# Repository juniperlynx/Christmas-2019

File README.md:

# 2019 Christmas Cards

Software and board layouts for my 2019 Christmas cards. These use an AtTiny84 to drive a 4x5 Charlieplexed LED array to display messages and run on a CR2032 coin cell. A cutout is included to hang them up.

Board design, software, and logo graphics by Juniper Starr and licensed CC BY 4.0. Graphics made with the Snowtop Caps font are property of [Deiter Steffmann](http://www.steffmann.de) and are free for noncommercial use only.

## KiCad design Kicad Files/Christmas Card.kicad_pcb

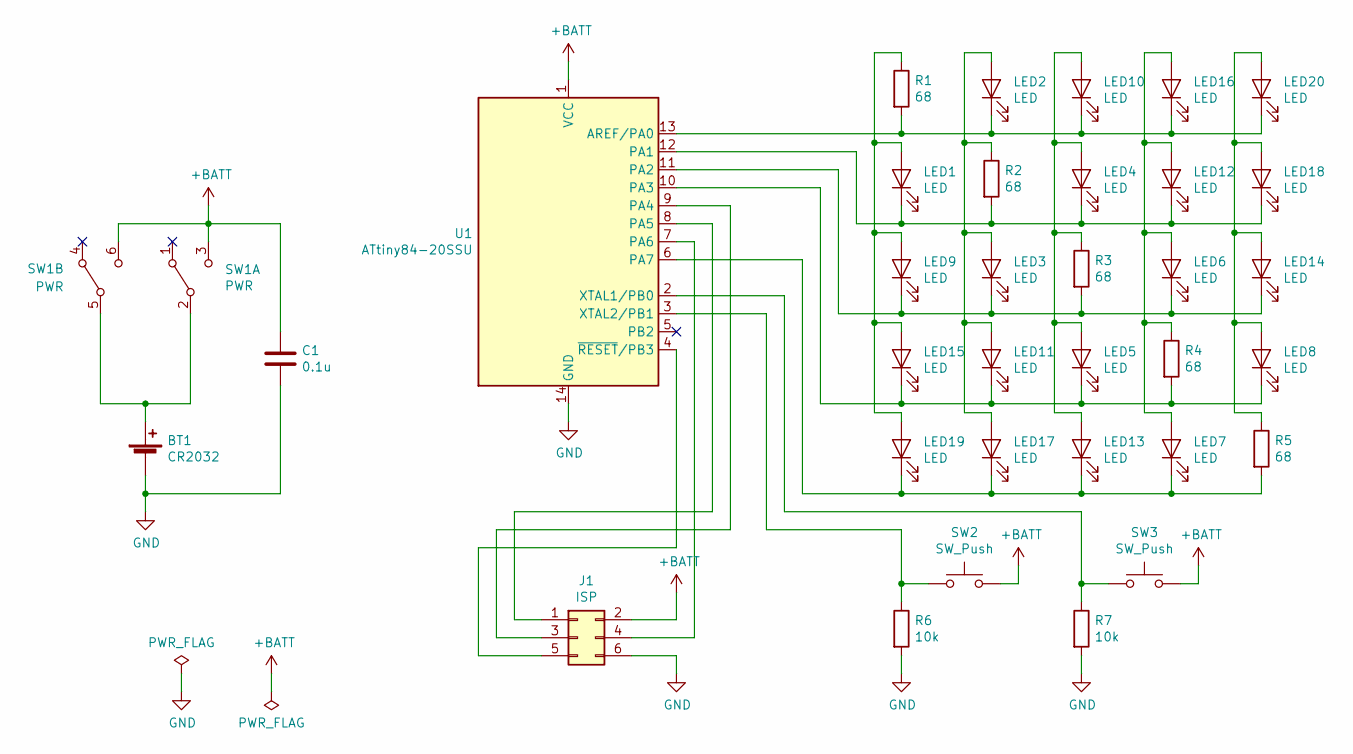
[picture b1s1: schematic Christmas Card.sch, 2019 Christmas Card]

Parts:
BT1: CR2032; BatteryStrap BC-2003-G-TR
C1: 0.1u; C_0805_2012Metric
J1: ISP; PinHeader_2x03_P2.54mm_Vertical
LED1, LED2, LED3, LED4, LED5, LED6, LED7, LED8, LED9, LED10, LED11, LED12, LED13, LED14, LED15, LED16, LED17, LED18, LED19, LED20: LED; LED_0805_2012Metric
R1, R2, R3, R4, R5: 68; R_0805_2012Metric
R6, R7: 10k; R_0805_2012Metric
SW1: PWR; SlideSwitch JS202011SQCN
SW2, SW3: SW_Push; SW_SPST_PTS645
U1: ATtiny84-20SSU; SOIC-14_3.9x8.7mm_P1.27mm

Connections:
+BATT: C1.1, J1.2, SW1.3 (C), SW1.6 (C), SW2.2, SW3.2, U1.1 (VCC); also elsewhere on the board
GND: BT1.2 (-), C1.2, J1.6, R6.2, R7.2, U1.14 (GND); also elsewhere on the board
unnamed: BT1.1 (+), SW1.2 (B), SW1.5 (B)
unnamed 3: J1.1, U1.8 (PA5); also elsewhere on the board
unnamed 4: J1.3, U1.9 (PA4); also elsewhere on the board
unnamed 5: J1.4, U1.7 (PA6); also elsewhere on the board
unnamed 6: J1.5, U1.4 (~RESET~/PB3); also elsewhere on the board
unnamed 7: LED1.1 (K), LED4.1 (K), LED12.1 (K), LED18.1 (K), R2.2, U1.12 (PA1); also elsewhere on the board
unnamed: LED1.2 (A), LED9.2 (A), LED15.2 (A), LED19.2 (A), R1.1
unnamed 9: LED2.1 (K), LED10.1 (K), LED16.1 (K), LED20.1 (K), R1.2, U1.13 (AREF/PA0); also elsewhere on the board
unnamed: LED4.2 (A), LED5.2 (A), LED10.2 (A), LED13.2 (A), R3.1
unnamed 11: LED5.1 (K), LED8.1 (K), LED11.1 (K), LED15.1 (K), R4.2, U1.10 (PA3); also elsewhere on the board
unnamed 12: LED2.2 (A), LED3.2 (A), LED11.2 (A), LED17.2 (A), R2.1; also elsewhere on the board
unnamed 13: LED6.2 (A), LED7.2 (A), LED12.2 (A), LED16.2 (A), R4.1; also elsewhere on the board
unnamed 14: LED7.1 (K), LED13.1 (K), LED17.1 (K), LED19.1 (K), R5.2, U1.6 (PA7); also elsewhere on the board
unnamed 15: LED3.1 (K), LED6.1 (K), LED9.1 (K), LED14.1 (K), R3.2, U1.11 (PA2); also elsewhere on the board
unnamed: LED8.2 (A), LED14.2 (A), LED18.2 (A), LED20.2 (A), R5.1
unnamed 17: R6.1, SW2.1, U1.3 (XTAL2/PB1); also elsewhere on the board
unnamed 18: R7.1, SW3.1, U1.2 (XTAL1/PB0); also elsewhere on the board

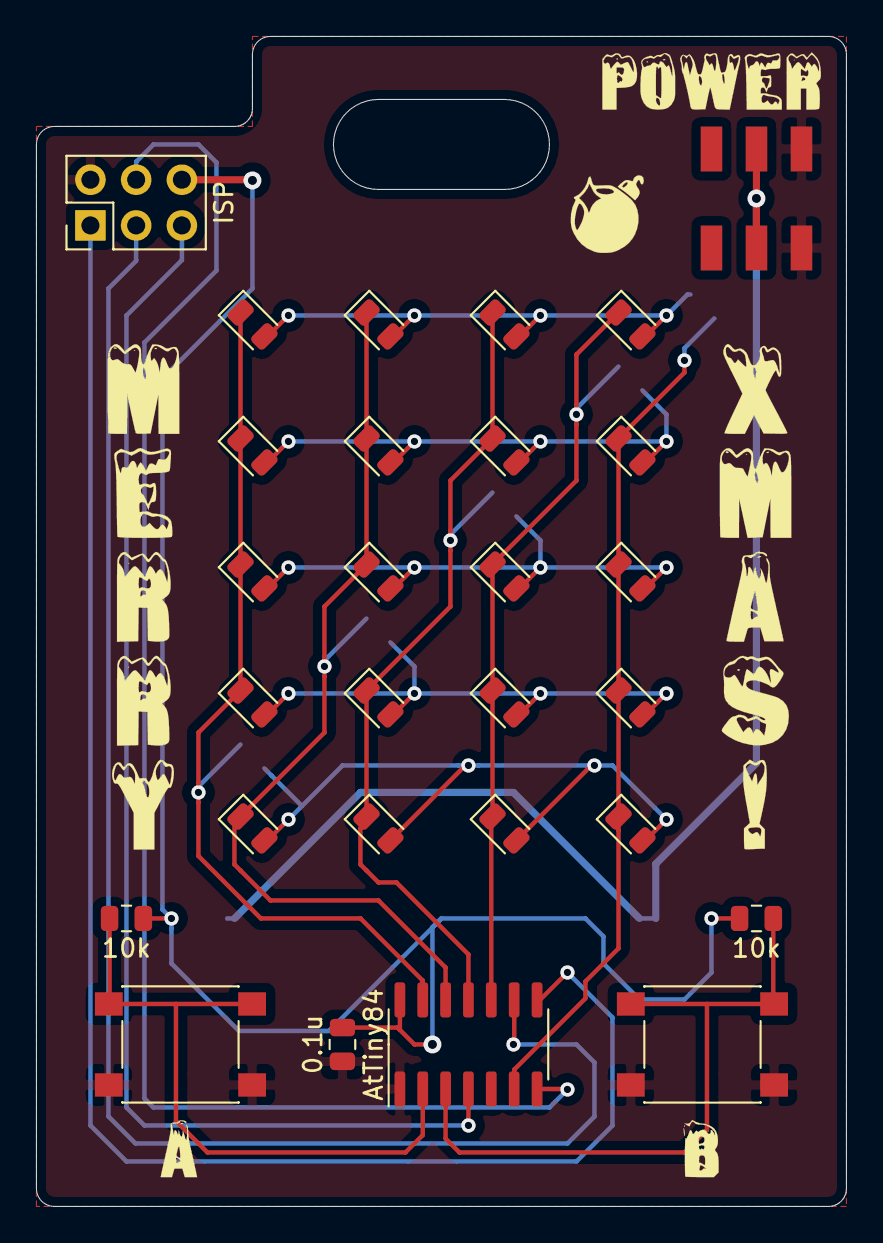
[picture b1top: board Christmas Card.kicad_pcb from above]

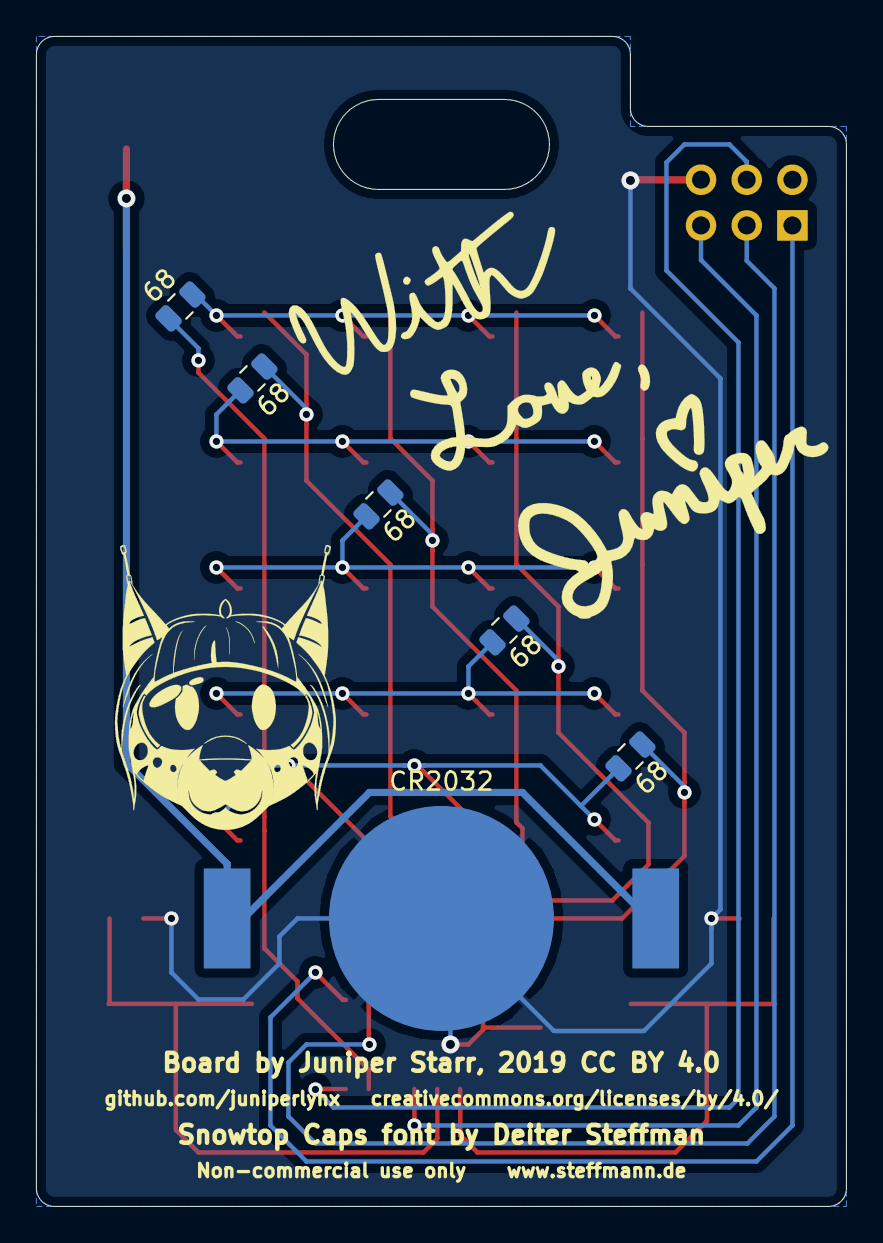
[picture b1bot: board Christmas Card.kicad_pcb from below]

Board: 2 copper layers, 45.0 x 65.0 mm, 34 parts (6 on the bottom side), 19 nets.

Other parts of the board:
AtTiny84: ATtiny84-20SSU; SOIC-14_3.9x8.7mm_P1.27mm
LED: LED; LED_0805_2012Metric
LED#2: LED; LED_0805_2012Metric

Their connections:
+BATT: AtTiny84.1; also elsewhere on the board
GND: AtTiny84.14; also elsewhere on the board
unnamed 3: AtTiny84.8; also elsewhere on the board
unnamed 4: AtTiny84.9; also elsewhere on the board
unnamed 5: AtTiny84.7; also elsewhere on the board
unnamed 6: AtTiny84.4; also elsewhere on the board
unnamed 7: AtTiny84.12; also elsewhere on the board
unnamed 9: AtTiny84.13; also elsewhere on the board
unnamed 11: AtTiny84.10; also elsewhere on the board
unnamed 12: LED.2; also elsewhere on the board
unnamed 13: LED#2.2; also elsewhere on the board
unnamed 14: AtTiny84.6; also elsewhere on the board
unnamed 15: AtTiny84.11, LED.1, LED#2.1; also elsewhere on the board
unnamed 17: AtTiny84.3; also elsewhere on the board
unnamed 18: AtTiny84.2; also elsewhere on the board

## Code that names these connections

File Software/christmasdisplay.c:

// Display function file for a Christmas card with a Charlieplexed display
// By:   _           _               
//      (_)_  _ _ _ (_)_ __  ___ _ _ 
//      | | || | ' \| | '_ \/ -_) '_|
//     _/ |\_,_|_||_|_| .__/\___|_|  
//    |__/            |_|  
// Filename: christmasdisplay.c
// Date: Nov 28, 2019

// Include AVR I/O defines, the delay function, and a 3x5 font
#include <avr/io.h>
#include "christmasdisplay.h"
#include "christmasfont.h"

// Lights an individual LED as specified. Expects PORTA and DDRA to be cleared first.
// I know this is uncreative, but eh...
// Physically mapped as follows:
//     4  9  14 19
//     3  8  13 18
//     2  7  12 17
//     1  6  11 16
//     0  5  10 15
void lightLED(uint8_t led) {
    // Set needed bits
    switch (led) {
        case 0 :
            DDRA |= _BV(PA0) | _BV(PA1);
            PORTA |= _BV(PA0);
            break;
        case 1 :
            DDRA |= _BV(PA0) | _BV(PA1);
            PORTA |= _BV(PA1);
            break;
        case 2 :
            DDRA |= _BV(PA0) | _BV(PA2);
            PORTA |= _BV(PA2);
            break;
        case 3 :
            DDRA |= _BV(PA0) | _BV(PA3);
            PORTA |= _BV(PA3);
            break;
        case 4 :
            DDRA |= _BV(PA0) | _BV(PA7);
            PORTA |= _BV(PA7);
            break;
        case 5 :
            DDRA |= _BV(PA0) | _BV(PA2);
            PORTA |= _BV(PA0);
            break;
        case 6 :
            DDRA |= _BV(PA1) | _BV(PA2);
            PORTA |= _BV(PA1);
            break;
        case 7 :
            DDRA |= _BV(PA1) | _BV(PA2);
            PORTA |= _BV(PA2);
            break;
        case 8 :
            DDRA |= _BV(PA1) | _BV(PA3);
            PORTA |= _BV(PA3);
            break;
        case 9 :
            DDRA |= _BV(PA1) | _BV(PA7);
            PORTA |= _BV(PA7);
            break;
        case 10 :
            DDRA |= _BV(PA0) | _BV(PA3);
            PORTA |= _BV(PA0);
            break;
        case 11 :
            DDRA |= _BV(PA1) | _BV(PA3);
            PORTA |= _BV(PA1);
            break;
        case 12 :
            DDRA |= _BV(PA2) | _BV(PA3);
            PORTA |= _BV(PA2);
            break;
        case 13 :
            DDRA |= _BV(PA2) | _BV(PA3);
            PORTA |= _BV(PA3);
            break;
        case 14 :
            DDRA |= _BV(PA2) | _BV(PA7);
            PORTA |= _BV(PA7);
            break;
        case 15 :
            DDRA |= _BV(PA0) | _BV(PA7);
            PORTA |= _BV(PA0);
            break;
        case 16 :
            DDRA |= _BV(PA1) | _BV(PA7);
            PORTA |= _BV(PA1);
            break;
        case 17 :
            DDRA |= _BV(PA2) | _BV(PA7);
            PORTA |= _BV(PA2);
            break;
        case 18 :
            DDRA |= _BV(PA3) | _BV(PA7);
            PORTA |= _BV(PA3);
            break;
        case 19 :
            DDRA |= _BV(PA3) | _BV(PA7);
            PORTA |= _BV(PA7);
            break;
    }
}

// Displays a bit corresponding to the current phase of the display update
// if the corresponding bit of the diaplay array is set.
void displayBit(uint8_t phase, uint8_t display[NUM_COLS]) {
    // Clear DDRA and PORTA
    DDRA = 0;
    PORTA = 0;

    // Light current phase's LED if a one is present in the corresponding bit
    if (display[phase / NUM_ROWS] >> (phase % NUM_ROWS) & 0x01) {
        lightLED(phase);
    }
}

// Wrapper to grab characters from the font function by column 
uint8_t getFontCol(char character, uint8_t column) {
    // If asking for anything beyond the third column, return zero
    if (column >= NUM_COLS - 1) {
        return 0x00;
    }
    // If asking for non printable characters, return zero
    else if ((int)character < 32 || (int)character > 126) {
        return 0x00;
    }
    // Otherwise, return the correct entry from the font variable in christmasfont.h
    else {
        return font[(int)character - 32][column];
    }
}

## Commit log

2019-11-25 Initial Software
2019-11-27 Add fonts and string support
2019-11-28 Add scrolling to text
2019-11-28 Expand font table
2019-11-29 Major reorganization to compress font table &c
2019-11-29 Minor font tweaks and further font compression.
2019-11-29 Add snow animation and mode switching

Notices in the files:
Kicad Files/Christmas Card.kicad_pcb:
github.com/juniperlynx creativecommons.org/licenses/by/4.0
Board by Juniper Starr, 2019 CC BY 4.0
